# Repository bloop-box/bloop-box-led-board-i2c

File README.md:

# Bloop Box LED Board with I2C

[Documentation](https://bloop-box.github.io/bloop-box-led-board-i2c)

I2C controlled RGB LED using the AW2013DNR IC

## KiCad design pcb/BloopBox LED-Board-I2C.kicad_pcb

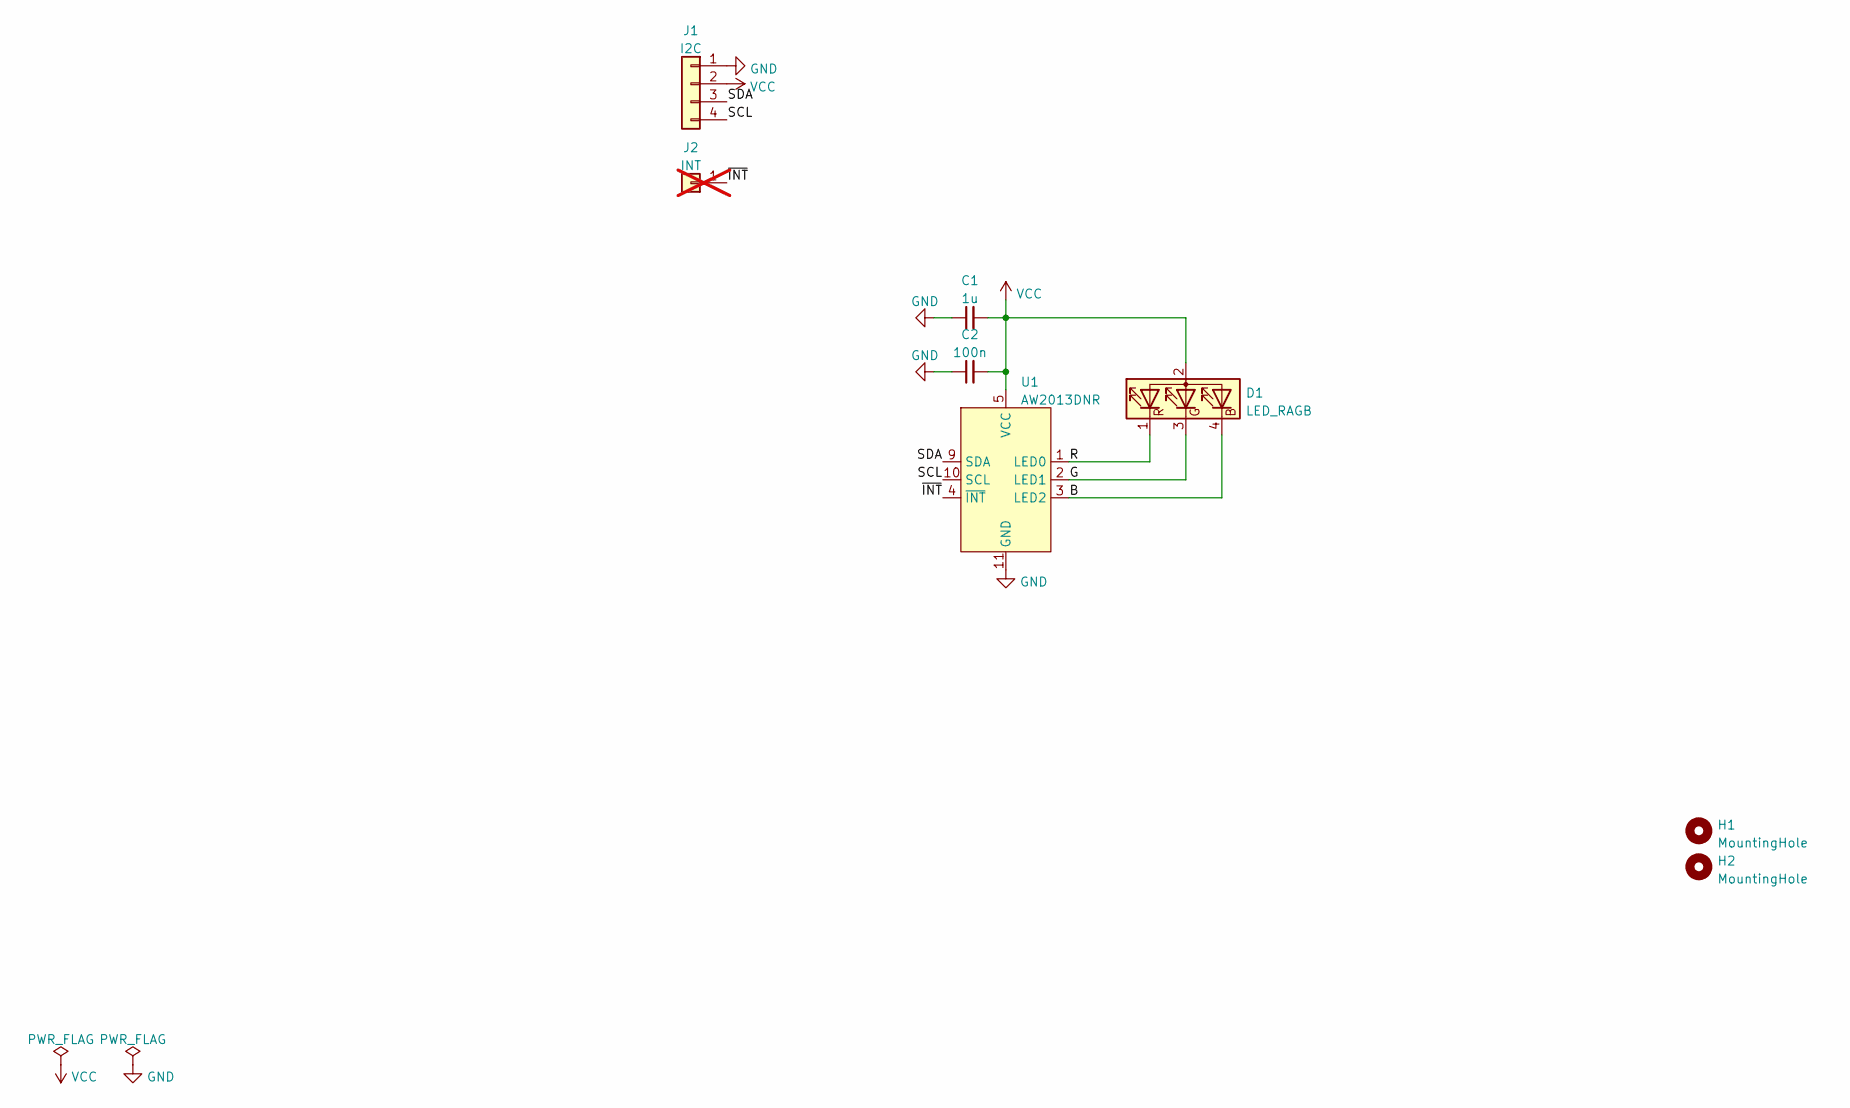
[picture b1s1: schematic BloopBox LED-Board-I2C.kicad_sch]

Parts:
C1: 1u; C_0402_1005Metric; LCSC C52923
C2: 100n; C_0402_1005Metric; LCSC C1525
D1: LED_RAGB; LED_D5.0mm-4_RGB_Staggered_Pins
H1, H2: MountingHole; MountingHole_3.2mm_M3_Pad
J1: I2C; JST_PH_S4B-PH-K_1x04_P2.00mm_Horizontal; LCSC C49994
J2: INT; PinHeader_1x01_P2.00mm_Vertical; not fitted
U1: AW2013DNR; DFN-10-1EP_2x2mm_P0.4mm_EP0.8x1.4; LCSC C252440

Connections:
/B: D1.4 (BK), U1.3 (LED2)
/G: D1.3 (GK), U1.2 (LED1)
/R: D1.1 (RK), U1.1 (LED0)
/SCL: J1.4, U1.10 (SCL)
/SDA: J1.3, U1.9 (SDA)
/~INT: J2.1, U1.4 (~INT)
GND: C1.1, C2.1, J1.1, U1.11 (GND)
VCC: C1.2, C2.2, D1.2 (A), J1.2, U1.5 (VCC)

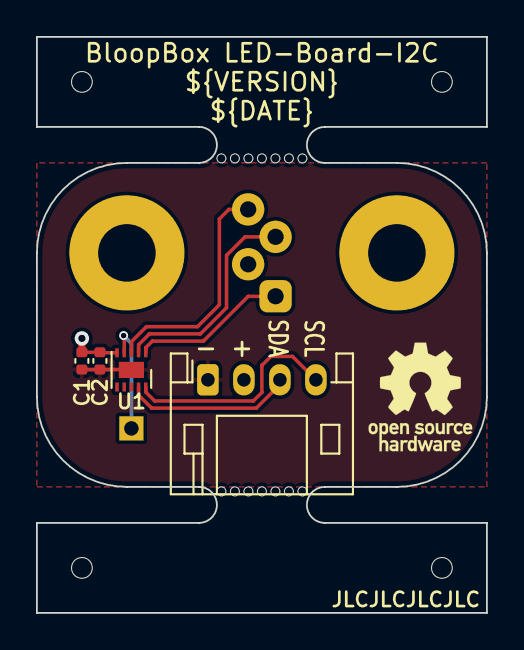
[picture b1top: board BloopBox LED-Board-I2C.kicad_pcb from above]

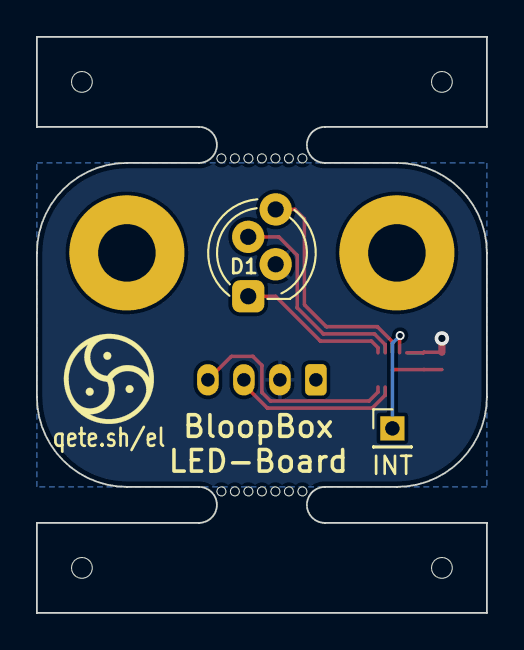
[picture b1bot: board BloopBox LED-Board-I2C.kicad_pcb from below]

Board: 2 copper layers, 25.0 x 32.0 mm, 10 parts (2 on the bottom side), 8 nets.

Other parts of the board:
mouse-bite-2mm-slot, mouse-bite-2mm-slot#2: VAL**; mouse-bite-2x5mm-slot-onesided

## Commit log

2023-01-03 feat: initial commit
2023-01-03 fix: add part numbers
    Add missing LSCS Part numbers
2023-01-03 fix: add pin description
2023-01-03 fix: add power flags
2023-01-03 fix: pcb filename changed
2023-01-03 chore(main): release 1.0.0
2023-01-04 feat: change LED controller to AW2013
    replace the IS31FL3199 with AW2013 and remove additional LED footprints
2023-01-04 chore(main): release 1.1.0
2023-01-04 fix: remove unused inner layers
2023-01-04 chore(main): release 1.1.1
2024-07-31 feat: flip sides of LED and connector
    Flip the LED to the bottom and the connector to the top to make it possible to have the connector assembled at the factory
    Also updating sources to KiCad 8
2024-07-31 fix: copper edge clearance
2024-07-31 chore(main): release 1.2.0
2024-08-29 ci: remove dependency between jobs
